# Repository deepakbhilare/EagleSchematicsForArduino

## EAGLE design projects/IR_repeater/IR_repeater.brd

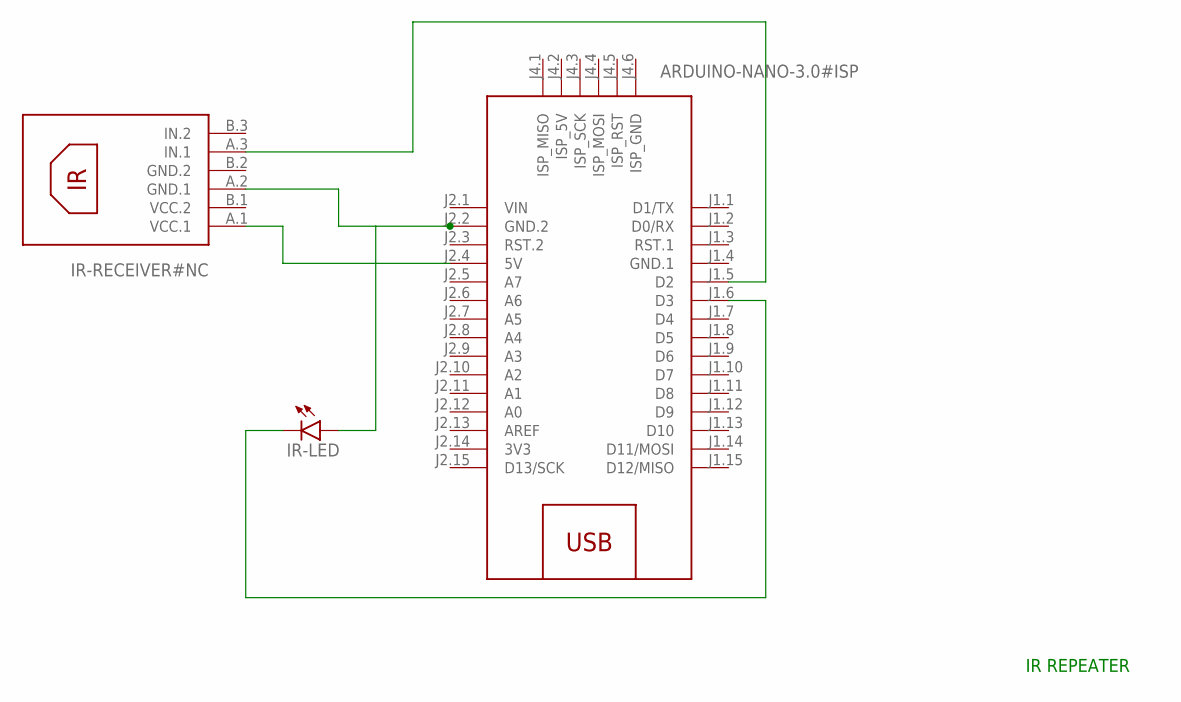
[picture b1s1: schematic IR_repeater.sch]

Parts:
IR-LED: SFH482
IR-RECEIVER: IR-RECEIVER#NC
M1: ARDUINO-NANO-3.0#ISP

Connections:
3V3: M1.J2.14 (3V3)
GND.1: M1.J1.4 (GND.1)
unnamed: IR-RECEIVER.A.1 (VCC.1), M1.J2.4 (5V)
unnamed: IR-RECEIVER.A.3 (IN.1), M1.J1.5 (D2)
unnamed: IR-LED.K (C), M1.J1.6 (D3)
unnamed: IR-LED.A, IR-RECEIVER.A.2 (GND.1), M1.J2.2 (GND.2)
VIN: M1.J2.1 (VIN)

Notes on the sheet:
IR REPEATER

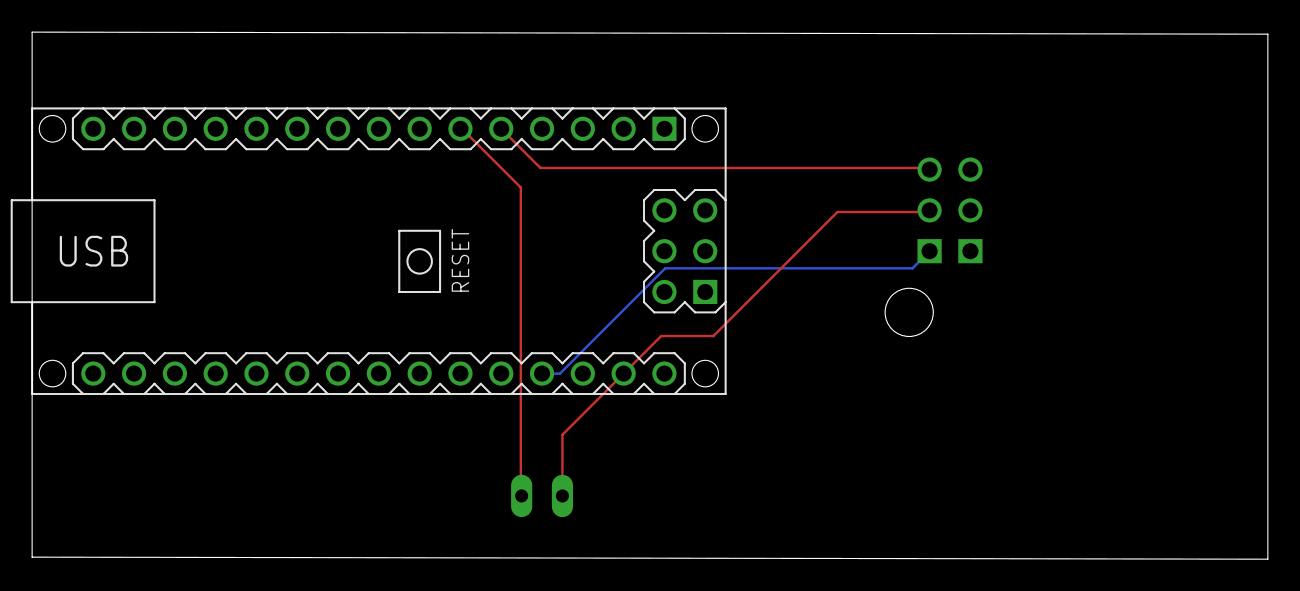
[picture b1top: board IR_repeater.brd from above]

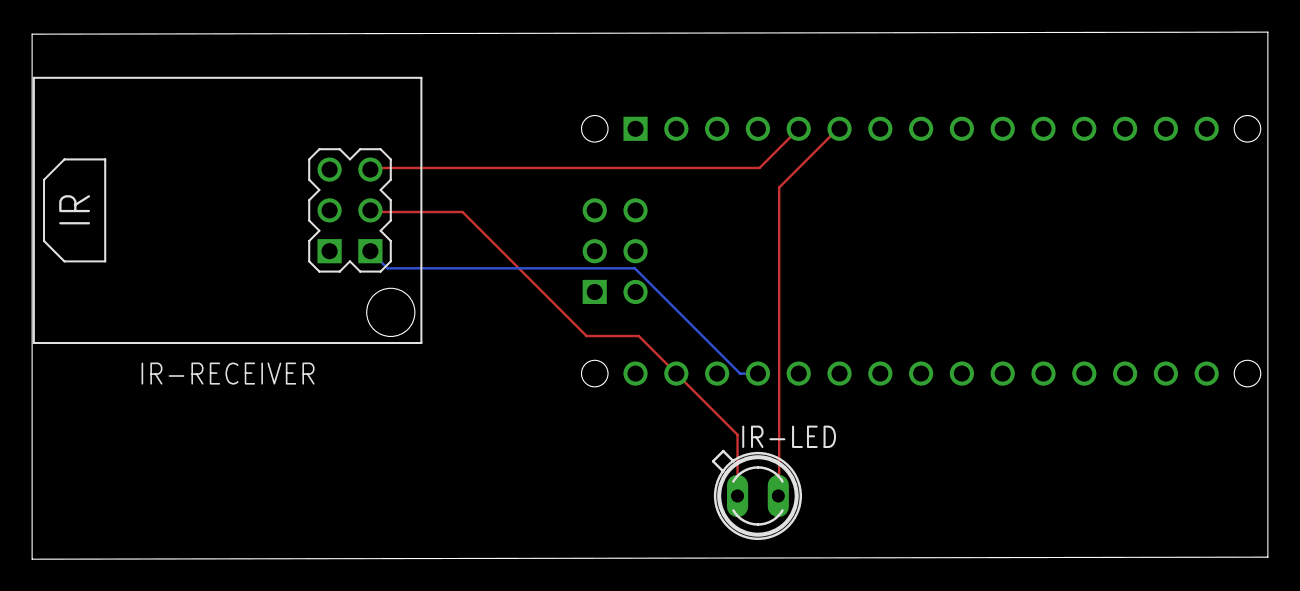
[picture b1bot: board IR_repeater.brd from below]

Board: 2 copper layers, 76.9 x 32.8 mm, 3 parts (2 on the bottom side), 4 nets.

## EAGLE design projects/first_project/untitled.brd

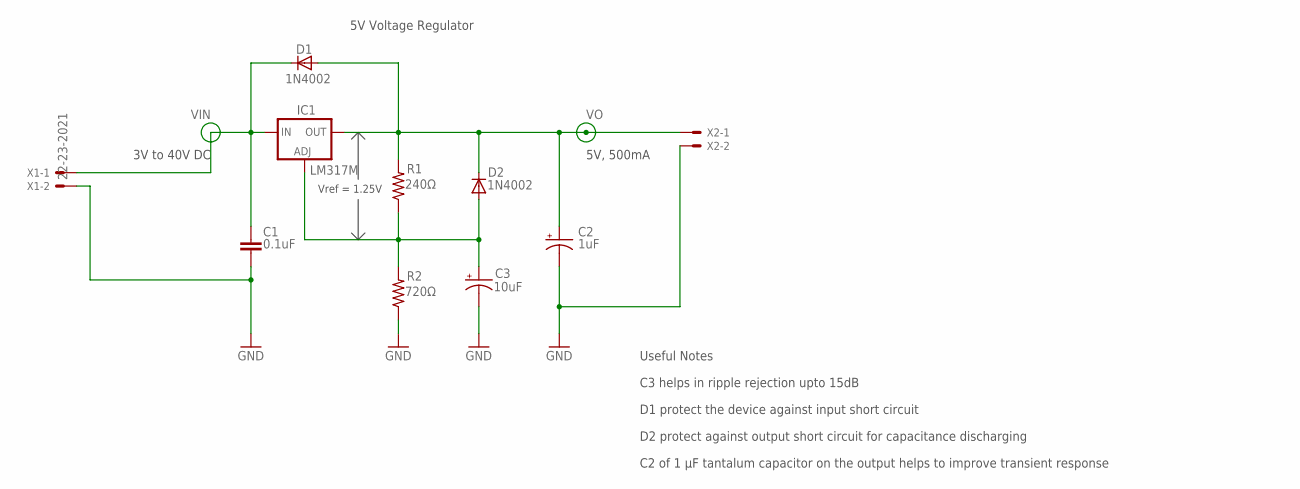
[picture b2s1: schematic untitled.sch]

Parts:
C1: 0.1uF; C075-052X106
C2: 1uF; 085CS_1AR
C3: 10uF; 085CS_1AR
D1, D2: 1N4002; DO41-10
IC1: LM317MBSTT3; SOT223; PARTNUMBER LM317M
R1: 240Ω; M0805
R2: 720Ω; M0805
X1, X2: 22-23-2021

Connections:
GND: C1.2, C2.-, C3.-, R2.1, X1.2, X2.2
unnamed: C3.+, D2.A, IC1.1 (ADJ), R1.1, R2.2
VIN: C1.1, D1.C, IC1.3 (IN), X1.1
VO: C2.+, D1.A, D2.C, IC1.4 (OUT), R1.2, X2.1

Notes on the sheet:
5V Voltage Regulator
C3 helps in ripple rejection upto 15dB
D1 protect the device against input short circuit
D2 protect against output short circuit for capacitance discharging
C2 of 1 µF tantalum capacitor on the output helps to improve transient response
Useful Notes
5V, 500mA
3V to 40V DC
Vref = 1.25V

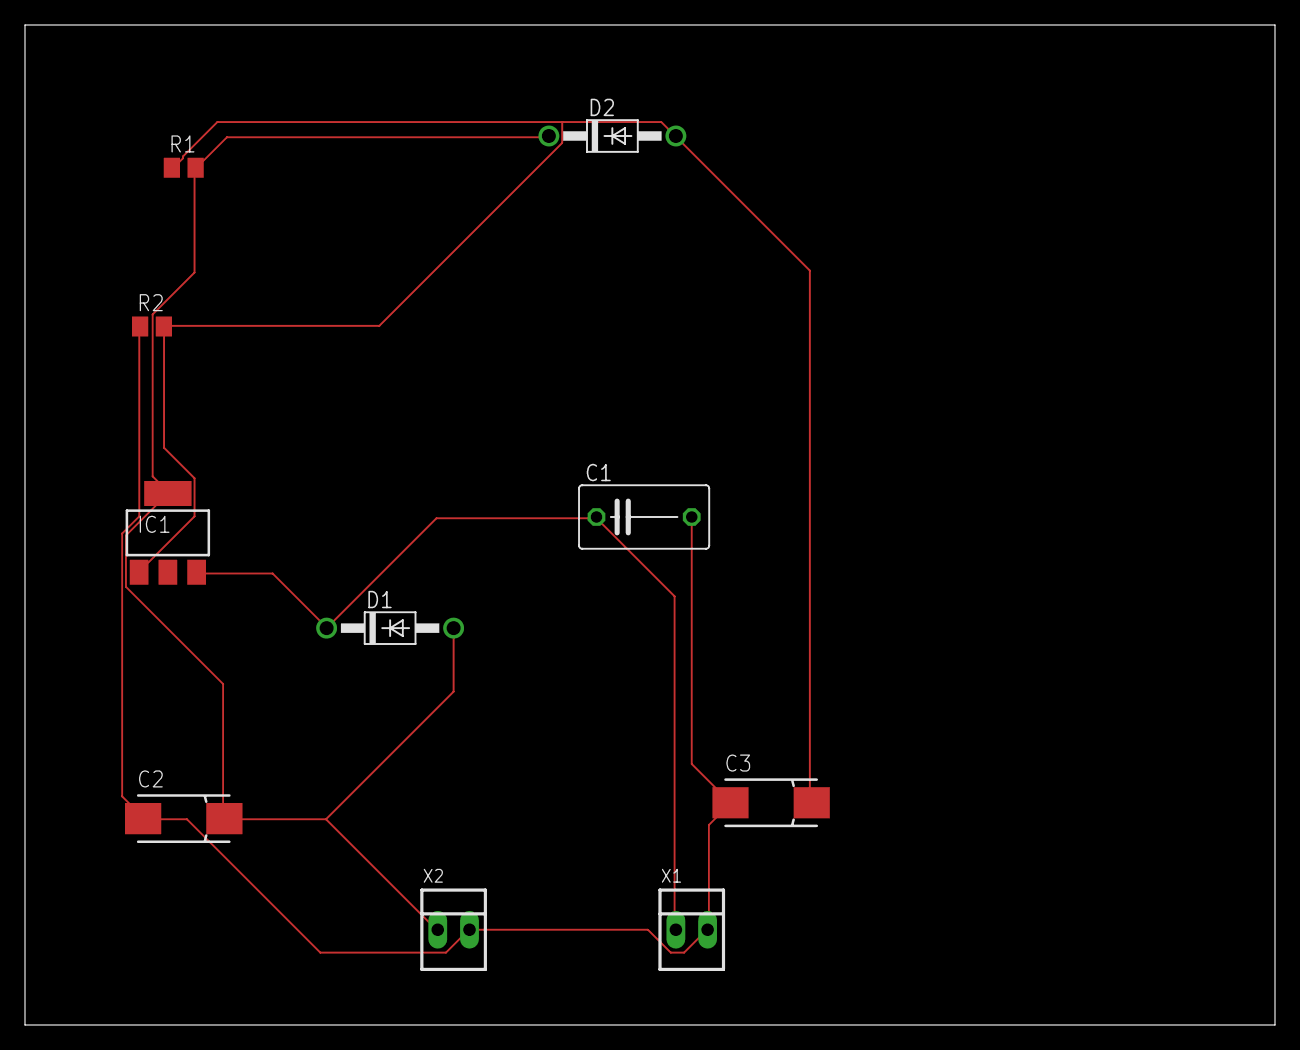
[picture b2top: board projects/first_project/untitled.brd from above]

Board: 2 copper layers, 100.0 x 80.0 mm, 10 parts (0 on the bottom side), 4 nets.

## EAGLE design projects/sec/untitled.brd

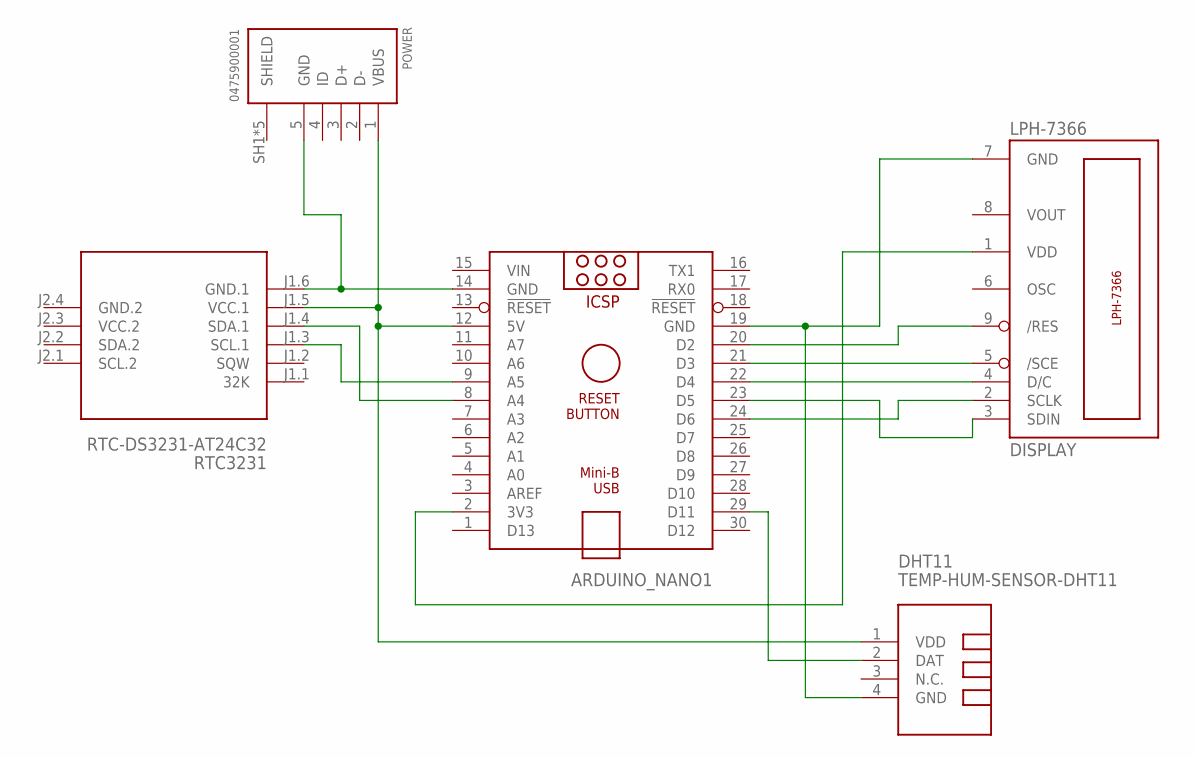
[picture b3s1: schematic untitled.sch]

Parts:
ARDUINO_NANO1: ARDUINO_NANO
DHT11: TEMP-HUM-SENSOR-DHT11
DISPLAY: LPH-7366
POWER: 0475900001
RTC3231: RTC-DS3231-AT24C32

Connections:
GND.2: RTC3231.J2.4 (GND.2)
unnamed: ARDUINO_NANO1.20 (D2), DISPLAY.9 (/RES)
unnamed: ARDUINO_NANO1.21 (D3), DISPLAY.5 (/SCE)
unnamed: ARDUINO_NANO1.22 (D4), DISPLAY.4 (D/C)
unnamed: ARDUINO_NANO1.23 (D5), DISPLAY.3 (SDIN)
unnamed: ARDUINO_NANO1.24 (D6), DISPLAY.2 (SCLK)
unnamed: ARDUINO_NANO1.2 (3V3), DISPLAY.1 (VDD)
unnamed: ARDUINO_NANO1.19 (GND), DHT11.4 (GND), DISPLAY.7 (GND)
unnamed: ARDUINO_NANO1.14 (GND), POWER.5 (GND), RTC3231.J1.6 (GND.1)
unnamed: ARDUINO_NANO1.12 (5V), DHT11.1 (VDD), POWER.1 (VBUS), RTC3231.J1.5 (VCC.1)
unnamed: ARDUINO_NANO1.8 (A4), RTC3231.J1.4 (SDA.1)
unnamed: ARDUINO_NANO1.9 (A5), RTC3231.J1.3 (SCL.1)
unnamed: ARDUINO_NANO1.29 (D11), DHT11.2 (DAT)
SHIELD: POWER.SH1 (SHIELD), POWER.SH2 (SHIELD), POWER.SH3 (SHIELD), POWER.SH4 (SHIELD), POWER.SH5 (SHIELD)
VCC.2: RTC3231.J2.3 (VCC.2)
VIN: ARDUINO_NANO1.15 (VIN)

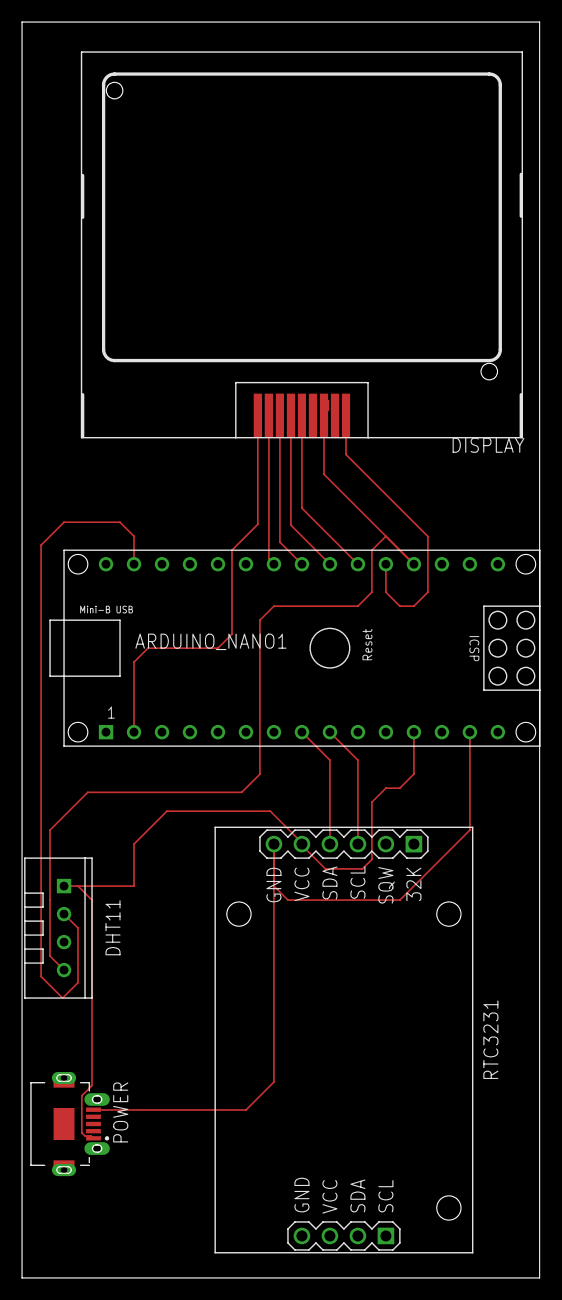
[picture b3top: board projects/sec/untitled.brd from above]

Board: 2 copper layers, 47.0 x 114.0 mm, 5 parts (0 on the bottom side), 13 nets.

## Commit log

2021-05-09 gitignore
2021-05-09 git ignore

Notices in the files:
parts and their libraries:
all_DIY: Released under the Creative Commons Attribution 4.0 International License: http://creativecommons.org/licenses/by/4.0
